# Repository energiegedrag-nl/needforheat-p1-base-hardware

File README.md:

# NeedForHeat P1-BASE hardware <!-- omit in toc -->

This repository contains the open hardware design files for the NeedForHeat P1-BASE, an extension module (BASE) for the back of an [M5Stack CoreInk](https://docs.m5stack.com/en/core/coreink). With it, the CoreInk reads [smart meters that adhere to the Dutch Smart Meter Requirements](https://github.com/energiegedrag-nl/dsmr-info) via the [P1 port](https://nl.wikipedia.org/wiki/P1-poort), while an existing P1 reader of the household keeps working.

> **Own deployment.** This repository is maintained by [energiegedrag-nl](https://github.com/energiegedrag-nl) and deployed under `energiegedrag.nl`. To run your own instance, replace `energiegedrag-nl` by your GitHub organisation and `energiegedrag.nl` by your domain (hosts used: `api.<domain>`, `manuals.<domain>`), consistently in configuration and build settings.

> **Version 3.0 (November 2026) is a design that has not been built or tested yet.** The previous version 2.7 (June 2024, with DIP switches) is available under the git tag `v2.7`. See [docs/design-v3.md](docs/design-v3.md) for the design and the list of points to verify on the first prototype.

## Table of contents <!-- omit in toc -->
- [General info](#general-info)
- [Producing](#producing)
  - [Printed Circuit Board](#printed-circuit-board)
  - [Enclosure](#enclosure)
- [Deploying](#deploying)
  - [Cost](#cost)
  - [Connecting](#connecting)
  - [Indicators](#indicators)
- [Developing](#developing)
- [Features](#features)
- [Status](#status)
- [License](#license)
- [Citation](#citation)
- [Credits](#credits)

## General info

The P1-BASE plugs into the 2x8 MI-BUS socket on the back of the CoreInk. The upper RJ12 socket (`J2`, *smart meter*) connects to the P1 port of the smart meter; the lower RJ12 socket (`J3`, *other P1 reader*) takes the cable of an existing P1 reader, as if it were connected to the meter itself.

In short (details in [docs/design-v3.md](docs/design-v3.md)):

* **Meter input** with a 1 kΩ pull-up and a Schmitt trigger, as in the v2.7 front end that read Landis+Gyr E350/E360 meters in the lab.
* **Active splitter**, powered by the meter: an existing reader keeps getting data when the CoreInk is off, asleep or crashed.
* **Data request** without DIP switches: the CoreInk (G26) and the existing reader can both request data; firmware can see whether the reader requests (G34).
* **Power from the P1 port**: on DSMR 5 meters the BASE can charge the CoreInk battery at 60 or 120 mA, switched by firmware and with a soft start that stays below the meter's fold-back limit.
* **Robust installation**: a crossed RJ12 cable or a cable in the wrong socket does no harm, and the firmware can tell which mistake was made.

The firmware is [needforheat-p1-reader-firmware](https://github.com/energiegedrag-nl/needforheat-p1-reader-firmware) (PlatformIO environment `M5STACK_COREINK_P1BASE_V3`).

## Producing

### Printed Circuit Board

The folder [pcb/jlcpcb](./pcb/jlcpcb) contains the files to have the PCB manufactured *and assembled* by [JLCPCB](https://jlcpcb.com); no soldering is needed:

1. Upload [`GERBER-needforheat-p1-base-hardware.zip`](./pcb/jlcpcb/GERBER-needforheat-p1-base-hardware.zip) on the [JLCPCB quote page](https://cart.jlcpcb.com/quote). Defaults are fine (2 layers, 1.6 mm).
2. Select *PCB Assembly*, top side, and upload [`BOM-needforheat-p1-base-hardware.csv`](./pcb/jlcpcb/BOM-needforheat-p1-base-hardware.csv) and [`CPL-needforheat-p1-base-hardware.csv`](./pcb/jlcpcb/CPL-needforheat-p1-base-hardware.csv).
3. The three through-hole parts (two RJ12 sockets, the 2x8 stacking header) are soldered by JLCPCB as well; accept the through-hole assembly option.
4. `R6` and `R15` are intentionally not fitted (see [assembly variants](docs/design-v3.md#8-production)).

Schematic and layout printouts: [docs/needforheat-p1-base-hardware-sch.pdf](docs/needforheat-p1-base-hardware-sch.pdf) and [docs/needforheat-p1-base-hardware-pcb.pdf](docs/needforheat-p1-base-hardware-pcb.pdf).

### Enclosure

The folder [enclosure](./enclosure) contains a parametric enclosure (CadQuery script) and exported STEP/STL files in [enclosure/fabrication](./enclosure/fabrication): a tray (*kuip*) that holds the PCB and centres the CoreInk with nocks in its LEGO-compatible holes, and a lid. Optional pockets take 8 x 1 mm steel discs opposite the CoreInk's built-in magnets. Print with PETG or let a 3D printing service make them (SLA resin or MJF nylon).

## Deploying

### Cost

Indicative, per module, November 2026, excluding VAT and shipping. A JLCPCB quote for 5 assembled boards came to € 43.68 (€ 8.70 per board); shipping to the Netherlands adds about € 20–25 per order.

| Item | Approx. price |
|---|---:|
| P1-BASE PCB, assembled (JLCPCB) | € 8–12 |
| Enclosure (3D printed) | € 3–6 |
| M5Stack CoreInk | € 36 |
| RJ12 cable 6P6C, straight (1:1), ≤ 0.5 m | € 3–6 |
| USB power adapter (only for DSMR 2/3 meters) | € 10–15 |

### Connecting

The CoreInk and the P1-BASE are shipped separately (each fits a letterbox parcel) and clicked together at home.

1. Hold the CoreInk with its screen facing you and the HAT connector (top edge) up. Push the P1-BASE onto its back so that the *smart meter* socket is at the top; it only fits this way round.
2. Unplug an existing P1 reader (if any) from the smart meter.
3. Plug the supplied **straight (1:1)** RJ12 cable into the *smart meter* socket and into the P1 port of the smart meter. Do not use a telephone cable: those are crossed. A crossed cable does no damage, but nothing works; the screen will say so.
4. Plug the existing P1 reader into the lower *other P1 reader* socket.

With a DSMR 2 or 3 meter (no power on the P1 port), also connect the USB power adapter to the CoreInk.

### Indicators

| LED | Meaning |
|---|---|
| green | blinks with the data from the meter |
| yellow | data is being requested from the meter |
| red | the CoreInk battery is being charged from the P1 port |

## Developing

You need [KiCad 10](https://www.kicad.org/download/) to change the design; the KiCad files are in [pcb](./pcb).

The schematic and the board are generated by scripts in [tools](./tools), so that the netlist, the placement and the documentation stay consistent:

* `python tools/gen_schematic.py` writes the schematic and the custom symbol library from the circuit description in the script.
* `"<KiCad>/bin/python.exe" tools/gen_pcb.py` builds the board from the schematic netlist, places the parts and routes the board with [Freerouting](https://github.com/freerouting/freerouting) (Java 25 needed).
* `python tools/sim/run_sims.py` runs SPICE checks with the ngspice library that ships with KiCad and writes [docs/simulation](docs/simulation).
* `python tools/export_fab.py` writes the JLCPCB files and the PDF printouts.

You may also edit the KiCad files by hand; then stop using the generators or port your changes into them.

## Features

Ready (in the design, not yet verified on hardware):

- [x] Active P1 splitter powered by the meter, open-drain output as DSMR prescribes.
- [x] Data request by firmware and by the existing reader (hardware OR); read-back of the reader's request.
- [x] Charging the CoreInk battery from DSMR 5 meters at 60/120 mA with soft start.
- [x] Protection against crossed cables and ESD; meter voltage measurement for diagnosis.
- [x] Three low-power indicator LEDs, test points.
- [x] All parts on the top side; full assembly by JLCPCB.
- [x] Enclosure that holds and centres the CoreInk.

To-do:

- [ ] Build and test a first prototype (see [the list of points to verify](docs/design-v3.md#10-open-points-to-verify)), including Landis+Gyr E360 meters and common P1 readers on the second socket.

## Status

Project is: _in progress_ (v3.0 design; v2.7 built and lab-tested in 2024).

## License

The hardware designs in this repository are available under the [CERN-OHL-P v2 license](./LICENSE).
Copyright 2024 [Research group Energy Transition, Windesheim University of Applied Sciences](https://windesheim.nl/energietransitie) (up to v2.7); copyright 2026 Henri ter Hofte (v3.0).

## Citation

If you use this repository in your research or work, please cite the following pre-print, which describes the overall NeedForHeat DataGear system of which this repository is a part:

> Ter Hofte, H., & van Ravenzwaaij, N. (2025). *NeedForHeat DataGear: An Open Monitoring System to Accelerate the Residential Heating Transition*. arXiv preprint arXiv:2509.06927. https://doi.org/10.48550/arXiv.2509.06927

**Note:** This is a pre-print submitted on 8 Sep 2025 and has not yet been peer-reviewed. For the full paper, see [https://arxiv.org/abs/2509.06927](https://arxiv.org/abs/2509.06927).

## Credits

Version 3.0:
* Henri ter Hofte · [@henriterhofte](https://github.com/henriterhofte)

Version 2.7 and earlier, made at the Research group Energy Transition, Windesheim University of Applied Sciences, as a collaborative effort of:
* Rick de Graaf · [@277r](https://github.com/277r)
* Gerwin ten Have · [@GerwintenHave](https://github.com/GerwintenHave)

with product owners:
* Henri ter Hofte · [@henriterhofte](https://github.com/henriterhofte)
* Marco Winkelman · [@MarcoW71](https://github.com/MarcoW71)

We use and gratefully acknowledge the efforts of the makers of:
* [Twomes P1 Gateway Hardware](https://github.com/energiegedrag-nl/twomes-p1-gateway-hardware), by Research group Energy Transition at Windesheim University of Applied Sciences, licensed under Apache 2.0
* [KiCad Libraries](https://kicad.github.io/), by the KiCad Development Team, licensed under [an adapted version of the CC-BY-SA 4.0 License](https://www.kicad.org/libraries/license/)
* [Freerouting](https://github.com/freerouting/freerouting), licensed under GPL-3.0 (used as a tool; no code included)
* [ngspice](https://ngspice.sourceforge.io/) and [CadQuery](https://github.com/CadQuery/cadquery) (used as tools)
* The mechanical data of the [M5Stack CoreInk](https://github.com/m5stack/M5_Hardware), by M5Stack

### AI assistance

Since November 2026, parts of this repository (the v3.0 design, its generators and documentation) have been made with [Claude Code](https://claude.com/claude-code) (Anthropic), under the author's direction and review. Commits made this way carry a `Co-Authored-By: Claude …` trailer. The author remains responsible for all content.

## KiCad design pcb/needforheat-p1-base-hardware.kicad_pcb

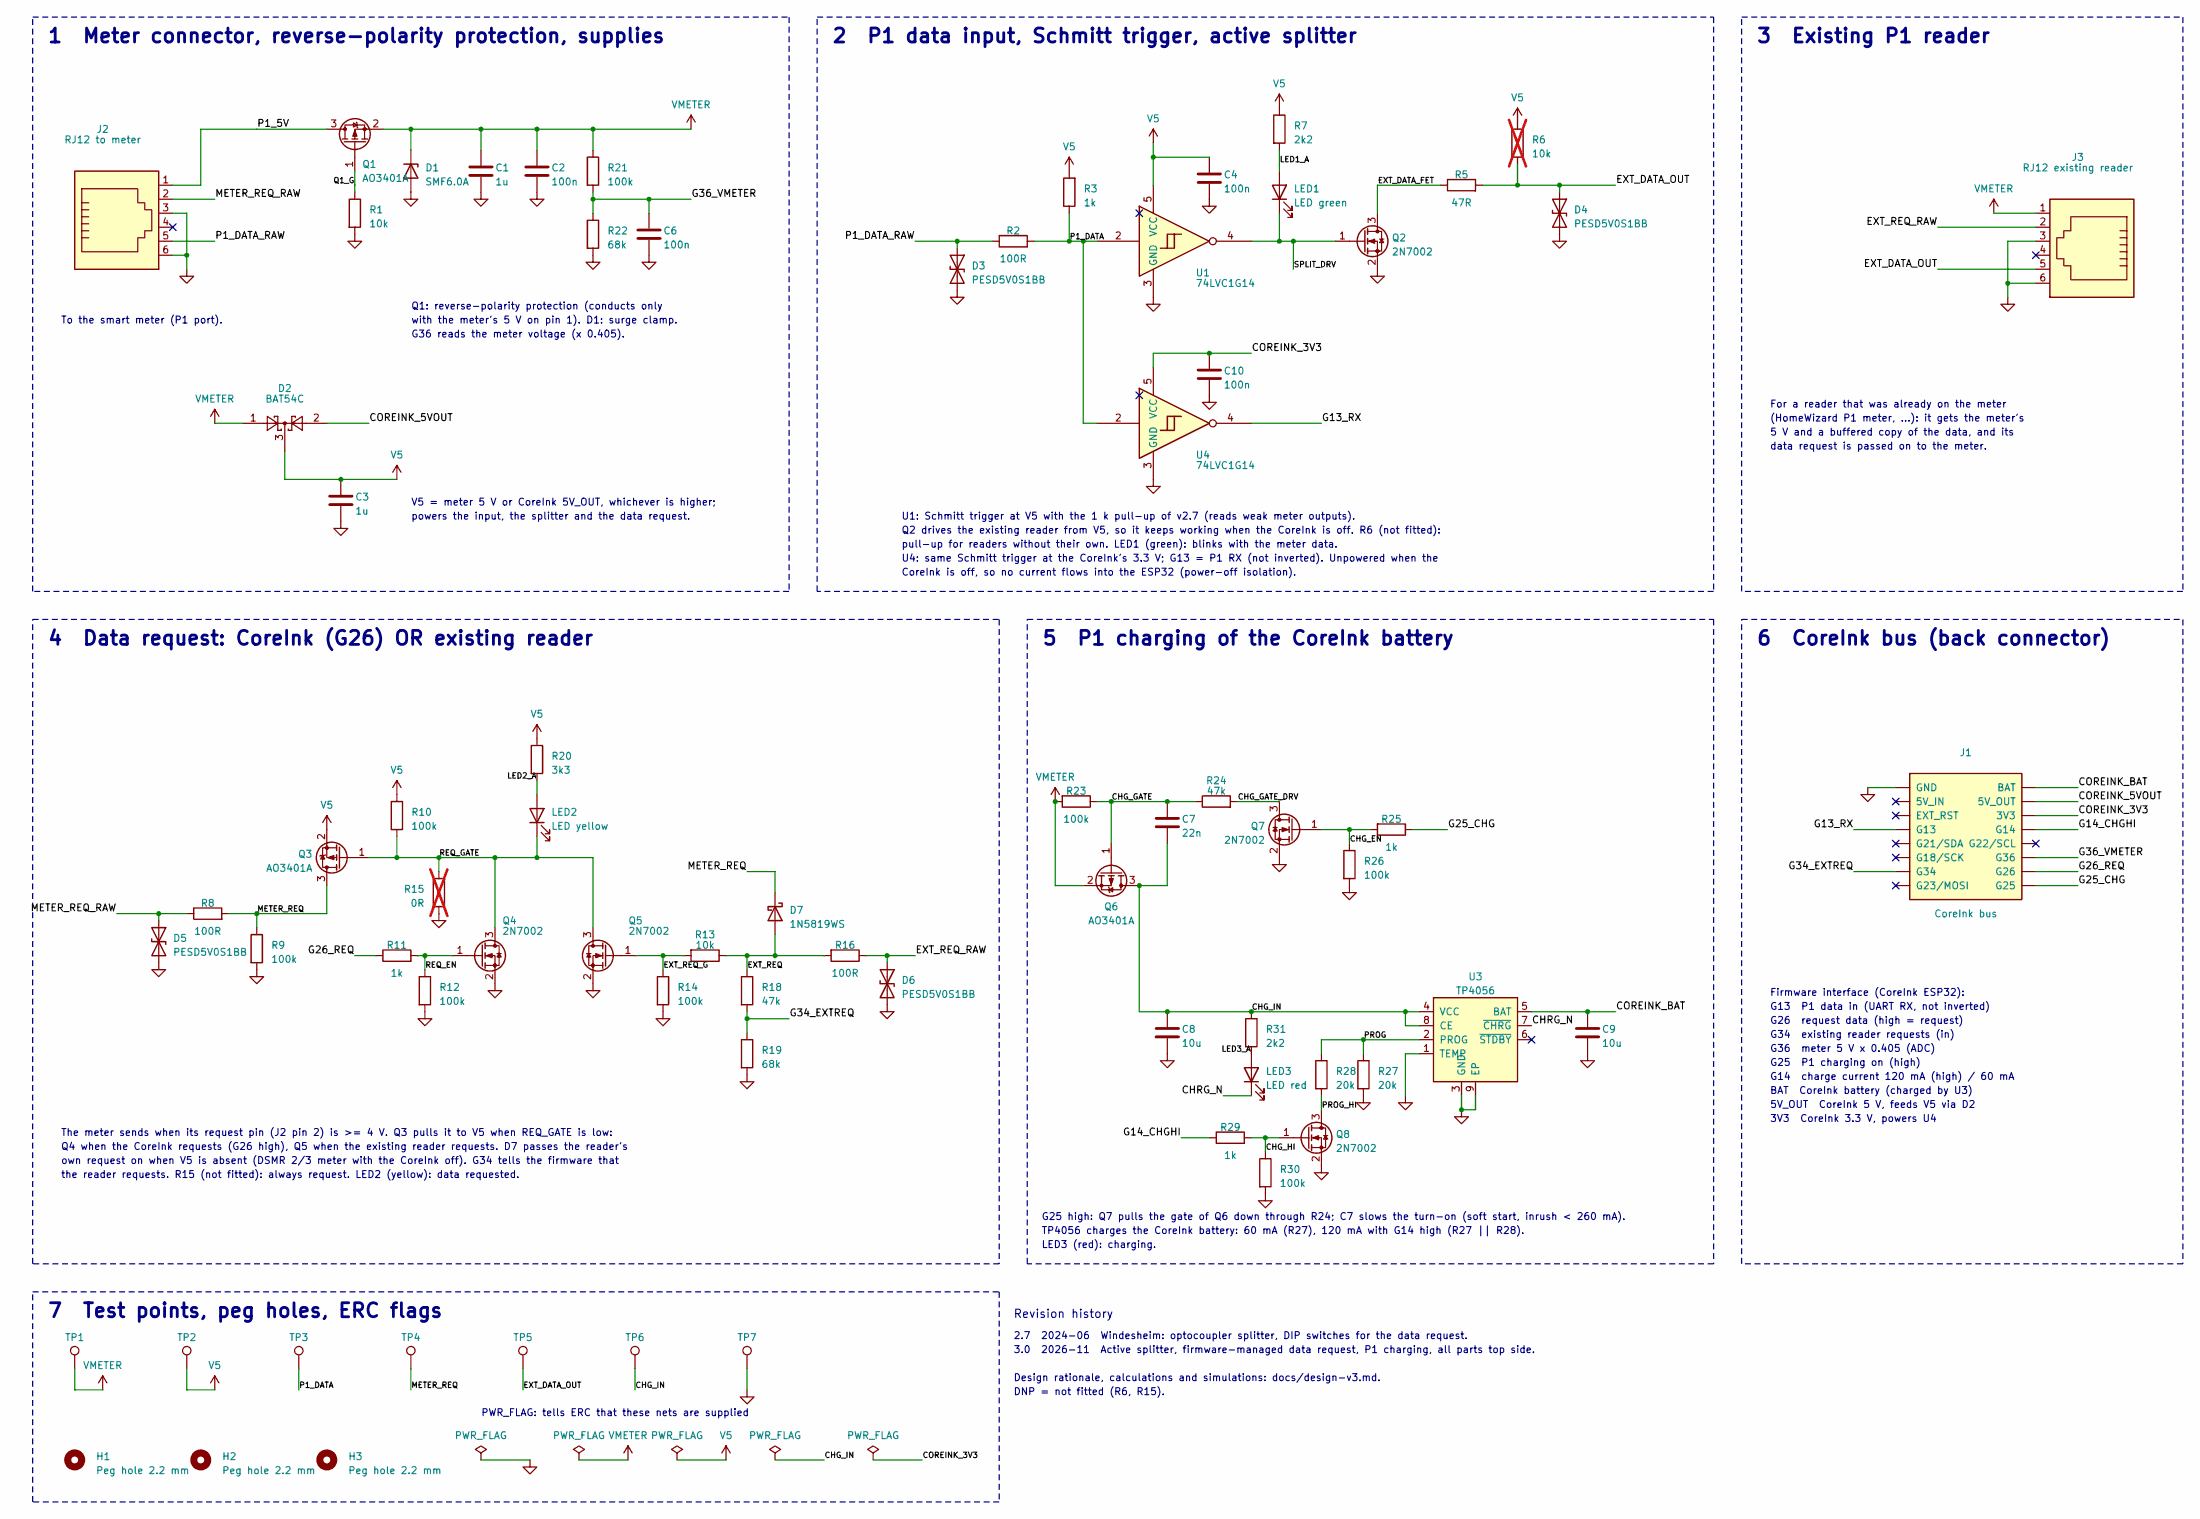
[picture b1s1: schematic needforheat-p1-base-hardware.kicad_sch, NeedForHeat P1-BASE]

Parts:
C1, C3: 1u; C_0603_1608Metric; LCSC C15849
C2, C4, C6, C10: 100n; C_0603_1608Metric; LCSC C14663
C7: 22n; C_0603_1608Metric; LCSC C21122
C8, C9: 10u; C_0805_2012Metric; LCSC C15850
D1: SMF6.0A; D_SMF; LCSC C178260
D2: BAT54C; SOT-23; LCSC C37704
D3, D4, D5, D6: PESD5V0S1BB; D_SOD-523; LCSC C2687128
D7: 1N5819WS; D_SOD-323; LCSC C191023
H1, H2, H3: Peg hole 2.2 mm; MountingHole_2.2mm_M2
J1: CoreInk bus; CoreInk_Bus_2x08_P2.54mm; LCSC C72555
J2: RJ12 to meter; RJ12_EVERCOM_5301-6P6C; LCSC C3097716
J3: RJ12 existing reader; RJ12_EVERCOM_5301-6P6C; LCSC C3097716
LED1: LED green; LED_0603_1608Metric; LCSC C12624
LED2: LED yellow; LED_0603_1608Metric; LCSC C2287
LED3: LED red; LED_0603_1608Metric; LCSC C2286
Q1, Q3, Q6: AO3401A; SOT-23; LCSC C15127
Q2, Q4, Q5, Q7, Q8: 2N7002; SOT-23; LCSC C8545
R1, R13: 10k; R_0603_1608Metric; LCSC C25804
R2, R8, R16: 100R; R_0603_1608Metric; LCSC C22775
R3, R11, R25, R29: 1k; R_0603_1608Metric; LCSC C21190
R5: 47R; R_0603_1608Metric; LCSC C23182
R6: 10k; R_0603_1608Metric; LCSC C25804; not fitted
R7, R31: 2k2; R_0603_1608Metric; LCSC C4190
R9, R10, R12, R14, R21, R23, R26, R30: 100k; R_0603_1608Metric; LCSC C25803
R15: 0R; R_0603_1608Metric; LCSC C21189; not fitted
R18, R24: 47k; R_0603_1608Metric; LCSC C25819
R19, R22: 68k; R_0603_1608Metric; LCSC C23231
R20: 3k3; R_0603_1608Metric; LCSC C22978
R27, R28: 20k; R_0603_1608Metric; LCSC C4184
TP1: VMETER; TestPoint_Pad_D1.0mm
TP2: V5; TestPoint_Pad_D1.0mm
TP3: P1_DATA; TestPoint_Pad_D1.0mm
TP4: METER_REQ; TestPoint_Pad_D1.0mm
TP5: EXT_DATA_OUT; TestPoint_Pad_D1.0mm
TP6: CHG_IN; TestPoint_Pad_D1.0mm
TP7: GND; TestPoint_Pad_D1.0mm
U1, U4: 74LVC1G14; SOT-23-5; LCSC C7835
U3: TP4056; SOIC-8-1EP_3.9x4.9mm_P1.27mm_EP2.29x3mm; LCSC C16581

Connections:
/CHG_EN: Q7.1 (G), R25.2, R26.1
/CHG_GATE: C7.1, Q6.1 (G), R23.1, R24.1
/CHG_GATE_DRV: Q7.3 (D), R24.2
/CHG_HI: Q8.1 (G), R29.2, R30.1
/CHG_IN: C7.2, C8.1, Q6.3 (D), R31.1, TP6.1, U3.4 (VCC), U3.8 (CE)
/CHRG_N: LED3.1 (K), U3.7 (~CHRG)
/COREINK_3V3: C10.1, J1.3V3, U4.5 (VCC)
/COREINK_5VOUT: D2.2, J1.5VOUT (5V_OUT)
/COREINK_BAT: C9.1, J1.BAT, U3.5 (BAT)
/EXT_DATA_FET: Q2.3 (D), R5.1
/EXT_DATA_OUT: D4.1 (A1), J3.5, R5.2, R6.1, TP5.1
/EXT_REQ: D7.2 (A), R13.1, R16.2, R18.1
/EXT_REQ_G: Q5.1 (G), R13.2, R14.1
/EXT_REQ_RAW: D6.1 (A1), J3.2, R16.1
/G13_RX: J1.G13, U4.4
/G14_CHGHI: J1.G14, R29.1
/G25_CHG: J1.G25, R25.1
/G26_REQ: J1.G26, R11.1
/G34_EXTREQ: J1.G34, R18.2, R19.1
/G36_VMETER: C6.1, J1.G36, R21.2, R22.1
/LED1_A: LED1.2 (A), R7.2
/LED2_A: LED2.2 (A), R20.2
/LED3_A: LED3.2 (A), R31.2
/METER_REQ: D7.1 (K), Q3.3 (D), R8.2, R9.1, TP4.1
/METER_REQ_RAW: D5.1 (A1), J2.2, R8.1
/P1_5V: J2.1, Q1.3 (D)
/P1_DATA: R2.2, R3.1, TP3.1, U1.2, U4.2
/P1_DATA_RAW: D3.1 (A1), J2.5, R2.1
/PROG: R27.1, R28.1, U3.2 (PROG)
/PROG_HI: Q8.3 (D), R28.2
/Q1_G: Q1.1 (G), R1.1
/REQ_EN: Q4.1 (G), R11.2, R12.1
/REQ_GATE: LED2.1 (K), Q3.1 (G), Q4.3 (D), Q5.3 (D), R10.1, R15.1
/SPLIT_DRV: LED1.1 (K), Q2.1 (G), U1.4
GND: C1.2, C2.2, C3.2, C4.2, C6.2, C8.2, C9.2, C10.2, D1.2 (A), D3.2 (A2), D4.2 (A2), D5.2 (A2), D6.2 (A2), J1.GND, J2.3, J2.6, J3.3, J3.6, Q2.2 (S), Q4.2 (S), Q5.2 (S), Q7.2 (S), Q8.2 (S), R1.2, R9.2, R12.2, R14.2, R15.2, R19.2, R22.2, R26.2, R27.2, R30.2, TP7.1, U1.3 (GND), U3.1 (TEMP), U3.3 (GND), U3.9 (EP), U4.3 (GND)
V5: C3.1, C4.1, D2.3, Q3.2 (S), R3.2, R6.2, R7.1, R10.2, R20.1, TP2.1, U1.5 (VCC)
VMETER: C1.1, C2.1, D1.1 (K), D2.1, J3.1, Q1.2 (S), Q6.2 (S), R21.1, R23.2, TP1.1

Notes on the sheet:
1 Meter connector, reverse-polarity protection, supplies
To the smart meter (P1 port).
Q1: reverse-polarity protection (conducts only
with the meter's 5 V on pin 1). D1: surge clamp.
G36 reads the meter voltage (x 0.405).
V5 = meter 5 V or CoreInk 5V_OUT, whichever is higher;
powers the input, the splitter and the data request.
2 P1 data input, Schmitt trigger, active splitter
U1: Schmitt trigger at V5 with the 1 k pull-up of v2.7 (reads weak meter outputs).
Q2 drives the existing reader from V5, so it keeps working when the CoreInk is off. R6 (not fitted):
pull-up for readers without their own. LED1 (green): blinks with the meter data.
U4: same Schmitt trigger at the CoreInk's 3.3 V; G13 = P1 RX (not inverted). Unpowered when the
CoreInk is off, so no current flows into the ESP32 (power-off isolation).
3 Existing P1 reader
For a reader that was already on the meter
(HomeWizard P1 meter, ...): it gets the meter's
5 V and a buffered copy of the data, and its
data request is passed on to the meter.
4 Data request: CoreInk (G26) OR existing reader
The meter sends when its request pin (J2 pin 2) is >= 4 V. Q3 pulls it to V5 when REQ_GATE is low:
Q4 when the CoreInk requests (G26 high), Q5 when the existing reader requests. D7 passes the reader's
own request on when V5 is absent (DSMR 2/3 meter with the CoreInk off). G34 tells the firmware that
the reader requests. R15 (not fitted): always request. LED2 (yellow): data requested.
5 P1 charging of the CoreInk battery
G25 high: Q7 pulls the gate of Q6 down through R24; C7 slows the turn-on (soft start, inrush < 260 mA).
TP4056 charges the CoreInk battery: 60 mA (R27), 120 mA with G14 high (R27 || R28).
LED3 (red): charging.
6 CoreInk bus (back connector)
Firmware interface (CoreInk ESP32):
G13 P1 data in (UART RX, not inverted)
G26 request data (high = request)
G34 existing reader requests (in)
G36 meter 5 V x 0.405 (ADC)
G25 P1 charging on (high)
G14 charge current 120 mA (high) / 60 mA
BAT CoreInk battery (charged by U3)
5V_OUT CoreInk 5 V, feeds V5 via D2
3V3 CoreInk 3.3 V, powers U4
7 Test points, peg holes, ERC flags
PWR_FLAG: tells ERC that these nets are supplied

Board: 2 copper layers, 72 parts (0 on the bottom side), 37 nets, no tracks yet.

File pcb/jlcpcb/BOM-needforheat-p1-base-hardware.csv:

Comment,Designator,Footprint,LCSC
1u,"C1,C3",C_0603_1608Metric,C15849
100n,"C2,C4,C6",C_0603_1608Metric,C14663
22n,C7,C_0603_1608Metric,C21122
10u,"C8,C9",C_0805_2012Metric,C15850
SMF5.0A,D1,D_SMF,C193402
BAT54C,D2,SOT-23,C37704
PESD5V0S1BB,"D3,D4,D5,D6",D_SOD-523,C2687128
1N5819WS,D7,D_SOD-323,C191023
CoreInk bus,J1,CoreInk_Bus_2x08_P2.54mm,C72555
RJ12 to meter / RJ12 existing reader,"J2,J3",RJ25_Wayconn_MJEA-660X1_Horizontal,C77859
LED green,LED1,LED_0603_1608Metric,C12624
LED yellow,LED2,LED_0603_1608Metric,C2287
LED red,LED3,LED_0603_1608Metric,C2286
AO3401A,"Q1,Q3,Q6",SOT-23,C15127
2N7002,"Q2,Q4,Q5,Q7,Q8",SOT-23,C8545
10k,"R1,R13,R32",R_0603_1608Metric,C25804
100R,"R2,R8,R16",R_0603_1608Metric,C22775
1k,"R3,R11,R25,R29",R_0603_1608Metric,C21190
4k7,R4,R_0603_1608Metric,C23162
47R,R5,R_0603_1608Metric,C23182
2k2,"R7,R31",R_0603_1608Metric,C4190
100k,"R9,R10,R12,R14,R21,R23,R26,R30",R_0603_1608Metric,C25803
47k,"R18,R24",R_0603_1608Metric,C25819
68k,"R19,R22",R_0603_1608Metric,C23231
3k3,R20,R_0603_1608Metric,C22978
20k,"R27,R28",R_0603_1608Metric,C4184
74LVC1G14,U1,SOT-23-5,C7835
TP4056,U3,SOIC-8-1EP_3.9x4.9mm_P1.27mm_EP2.29x3mm,C16581

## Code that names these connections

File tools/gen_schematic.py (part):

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    s.place("R22", 116.84, 54.61)
    s.place("C6", 127.0, 54.61)
    s.wire("J2.1", (45.72, 45.72), (45.72, 35.56), (55.88, 35.56), "Q1.3", first="v")
    s.label("P1_5V", (55.88, 35.56))
    s.wire("Q1.1", (73.66, 45.72), "R1.1")
    s.label("Q1_G", (73.66, 45.72), "l", 1.0)
    s.power("GND", "R1.2")
    s.wire("Q1.2", (83.82, 35.56), (96.52, 35.56), (106.68, 35.56), (116.84, 35.56), (134.62, 35.56))
    s.power("VMETER", (134.62, 35.56))
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    s.wire("R21.2", (116.84, 48.26), "R22.1")
    s.wire((116.84, 48.26), (127.0, 48.26), (134.62, 48.26))
    s.wire((127.0, 48.26), "C6.1")
    s.label("G36_VMETER", (134.62, 48.26))
    s.wire("J2.3", (43.18, 50.8), (43.18, 58.42), (43.18, 60.96))
    s.wire("J2.6", (43.18, 58.42))
    s.power("GND", (43.18, 60.96))
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    s.place("U4", 210.82, 88.9)
    s.place("C10", 215.9, 80.01)
    s.wire((162.56, 55.88), (170.18, 55.88), "R2.1")
    s.label("P1_DATA_RAW", (162.56, 55.88), "l")
    s.wire((170.18, 55.88), "D3.1")
    s.power("GND", "D3.2")
    s.wire("R2.2", (190.5, 55.88), (193.04, 55.88), "U1.2")
    s.wire((193.04, 55.88), "U4.2", first="v")
    s.label("P1_DATA", (190.5, 55.88), "r", 1.0)
    s.wire("R3.1", (190.5, 55.88))
    s.power("V5", "R3.2")
    s.wire("U1.5", (205.74, 40.64), (205.74, 38.1))
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    s.power("GND", "U1.3")
    s.wire("U1.4", (228.6, 55.88), (231.14, 55.88), "Q2.1")
    s.wire((231.14, 55.88), (231.14, 60.96))
    s.label("SPLIT_DRV", (231.14, 60.96), "r", 1.0)
    s.wire("LED1.1", (228.6, 55.88))
    s.wire("LED1.2", (228.6, 41.91), "R7.2")
    s.label("LED1_A", (228.6, 41.91), "r", 1.0)
    s.power("V5", "R7.1")
    s.power("GND", "Q2.2")
    s.wire("Q2.3", (246.38, 45.72), "R5.1", first="v")
    s.label("EXT_DATA_FET", (246.38, 45.72), "r", 1.0)
    s.wire("R5.2", (271.78, 45.72), (279.4, 45.72), (289.56, 45.72))
    s.wire("R6.1", (271.78, 45.72))
    s.power("V5", "R6.2")
    s.wire((279.4, 45.72), "D4.1")
    s.power("GND", "D4.2")
    s.label("EXT_DATA_OUT", (289.56, 45.72))
    s.wire("U4.5", (205.74, 76.2), (215.9, 76.2), (223.52, 76.2))
    s.wire((215.9, 76.2), "C10.1")
    s.power("GND", "C10.2")
    s.label("COREINK_3V3", (223.52, 76.2))
    s.power("GND", "U4.3")
    s.wire("U4.4", (236.22, 88.9))
    s.label("G13_RX", (236.22, 88.9))
    s.note("U1: Schmitt trigger at V5 with the 1 k pull-up of v2.7 (reads weak meter outputs).", 160.02, 106.68)
    s.note("Q2 drives the existing reader from V5, so it keeps working when the CoreInk is off. R6 (not fitted):", 160.02, 109.22)
    s.note("pull-up for readers without their own. LED1 (green): blinks with the meter data.", 160.02, 111.76)
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    s.place("R16", 154.94, 185.42, rot=270)
    s.place("D6", 162.56, 190.5, rot=270)
    s.wire((22.86, 177.8), (30.48, 177.8), "R8.1")
    s.label("METER_REQ_RAW", (22.86, 177.8), "l")
    s.wire((30.48, 177.8), "D5.1")
    s.power("GND", "D5.2")
    s.wire("R8.2", (48.26, 177.8), (60.96, 177.8), "Q3.3")
    s.label("METER_REQ", (48.26, 177.8), "r", 1.0)
    s.wire((48.26, 177.8), "R9.1")
    s.power("GND", "R9.2")
    s.power("V5", "Q3.2")
    s.wire("Q3.1", (73.66, 167.64), (81.28, 167.64), (91.44, 167.64), (99.06, 167.64), (109.22, 167.64))
    s.label("REQ_GATE", (81.28, 167.64), "r", 1.0)
    s.wire("R10.1", (73.66, 167.64))
    s.power("V5", "R10.2")
    s.wire((81.28, 167.64), "R15.1")
    s.power("GND", "R15.2")
    s.wire("LED2.1", (99.06, 167.64))
    s.wire("LED2.2", "R20.2")
    s.label("LED2_A", "R20.2", "l", 1.0)
    s.power("V5", "R20.1")
    s.wire("Q4.3", (91.44, 167.64))
    s.power("GND", "Q4.2")
    s.wire((66.04, 185.42), "R11.1")
    s.label("G26_REQ", (66.04, 185.42), "l")
    s.wire("R11.2", (78.74, 185.42), "Q4.1")
    s.wire((78.74, 185.42), "R12.1")
    s.label("REQ_EN", "R12.1", "r", 1.0)
    s.power("GND", "R12.2")
    s.wire("Q5.3", (109.22, 167.64))
    s.power("GND", "Q5.2")
    s.wire("Q5.1", (121.92, 185.42), "R13.2")
    s.wire((121.92, 185.42), "R14.1")
    s.label("EXT_REQ_G", "R14.1", "r", 1.0)
    s.power("GND", "R14.2")
    s.wire("R13.1", (137.16, 185.42), (142.24, 185.42), "R16.2")
    s.wire((137.16, 185.42), "R18.1")
    s.label("EXT_REQ", "R18.1", "r", 1.0)
    s.wire((142.24, 185.42), "D7.2")
    s.wire("D7.1", (142.24, 170.18), (137.16, 170.18))
    s.label("METER_REQ", (137.16, 170.18), "l")
    s.wire("R18.2", (137.16, 196.85), "R19.1")
    s.wire((137.16, 196.85), (144.78, 196.85))
    s.label("G34_EXTREQ", (144.78, 196.85))
    s.power("GND", "R19.2")
    s.wire("R16.1", (162.56, 185.42), (167.64, 185.42))
    s.wire((162.56, 185.42), "D6.1")
    s.power("GND", "D6.2")
    s.label("EXT_REQ_RAW", (167.64, 185.42))
    s.note("The meter sends when its request pin (J2 pin 2) is >= 4 V. Q3 pulls it to V5 when REQ_GATE is low:", 12.7, 218.44)
    s.note("Q4 when the CoreInk requests (G26 high), Q5 when the existing reader requests. D7 passes the reader's", 12.7, 220.98)
    s.note("own request on when V5 is absent (DSMR 2/3 meter with the CoreInk off). G34 tells the firmware that", 12.7, 223.52)
    s.note("the reader requests. R15 (not fitted): always request. LED2 (yellow): data requested.", 12.7, 226.06)
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    s.wire("R23.2", (200.66, 172.72), "Q6.2", first="v")
    s.power("VMETER", "R23.2")
    s.wire("R23.1", (210.82, 157.48), (220.98, 157.48), "R24.1")
    s.label("CHG_GATE", (210.82, 157.48), "r", 1.0)
    s.wire("Q6.1", (210.82, 157.48))
    s.wire("C7.1", (220.98, 157.48))
    s.wire("R24.2", "Q7.3")
    s.label("CHG_GATE_DRV", "R24.2", "r", 1.0)
    s.power("GND", "Q7.2")
    s.wire("Q7.1", (254.0, 162.56), "R25.2")
    s.wire((254.0, 162.56), "R26.1")
    s.label("CHG_EN", "R26.1", "r", 1.0)
    s.power("GND", "R26.2")
    s.wire("R25.1", (271.78, 162.56))
    s.label("G25_CHG", (271.78, 162.56))
    s.wire("C7.2", (220.98, 172.72), "Q6.3")
    s.wire("Q6.3", (215.9, 195.58), (220.98, 195.58), (236.22, 195.58), (264.16, 195.58), "U3.4", first="v")
    s.label("CHG_IN", (236.22, 195.58), "r", 1.0)
    s.wire((220.98, 195.58), "C8.1")
    s.power("GND", "C8.2")
    s.wire((236.22, 195.58), "R31.1")
    s.wire("R31.2", "LED3.2")
    s.label("LED3_A", "R31.2", "l", 1.0)
    s.stub("LED3.1", "CHRG_N", 5.08, "l")
    s.wire("U3.8", (264.16, 198.12), (264.16, 195.58))
    s.wire("U3.1", (264.16, 203.2), (264.16, 210.82))
    s.power("GND", (264.16, 210.82))
    s.wire("U3.2", (256.54, 200.66), (248.92, 200.66))
    s.label("PROG", (256.54, 200.66), "r", 1.0)
    s.wire((256.54, 200.66), "R27.1")
    s.power("GND", "R27.2")
    s.wire((248.92, 200.66), "R28.1")
    s.wire("R28.2", "Q8.3")
    s.label("PROG_HI", "Q8.3", "r", 1.0)
    s.power("GND", "Q8.2")
    s.wire("R29.2", (238.76, 218.44), "Q8.1")
    s.wire((238.76, 218.44), "R30.1")
    s.label("CHG_HI", "R30.1", "r", 1.0)
    s.power("GND", "R30.2")
    s.wire((223.52, 218.44), "R29.1")
    s.label("G14_CHGHI", (223.52, 218.44), "l")
    x3, y3 = s.pin("U3.3")
    s.wire("U3.3", (x3, y3 + 2.54), "U3.9", first="h")
    s.power("GND", (x3, y3 + 2.54))
    s.label("CHRG_N", "U3.7")
    s.wire("U3.5", (297.18, 195.58), (302.26, 195.58))
    s.wire((297.18, 195.58), "C9.1")
    s.power("GND", "C9.2")
    s.label("COREINK_BAT", (302.26, 195.58))
    s.note("G25 high: Q7 pulls the gate of Q6 down through R24; C7 slows the turn-on (soft start, inrush < 260 mA).", 198.12, 233.68)
    s.note("TP4056 charges the CoreInk battery: 60 mA (R27), 120 mA with G14 high (R27 || R28).", 198.12, 236.22)
    s.note("LED3 (red): charging.", 198.12, 238.76)
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    s.power("GND", (x - 5.08, y))
    s.stub("J1.G13", "G13_RX", 7.62, "l")
    s.stub("J1.G34", "G34_EXTREQ", 7.62, "l")
    for pin, net in (("BAT", "COREINK_BAT"), ("5VOUT", "COREINK_5VOUT"), ("3V3", "COREINK_3V3"), ("G14", "G14_CHGHI"), ("G36", "G36_VMETER"),
                     ("G26", "G26_REQ"), ("G25", "G25_CHG")):
        s.stub("J1." + pin, net, 7.62)
    for i, t in enumerate(["Firmware interface (CoreInk ESP32):",
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

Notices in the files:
pcb/needforheat-p1-base-hardware.kicad_pcb:
energiegedrag.nl - CERN-OHL-P v2
pcb/needforheat-p1-base-hardware.kicad_sch:
Licensed under CERN-OHL-P v2
